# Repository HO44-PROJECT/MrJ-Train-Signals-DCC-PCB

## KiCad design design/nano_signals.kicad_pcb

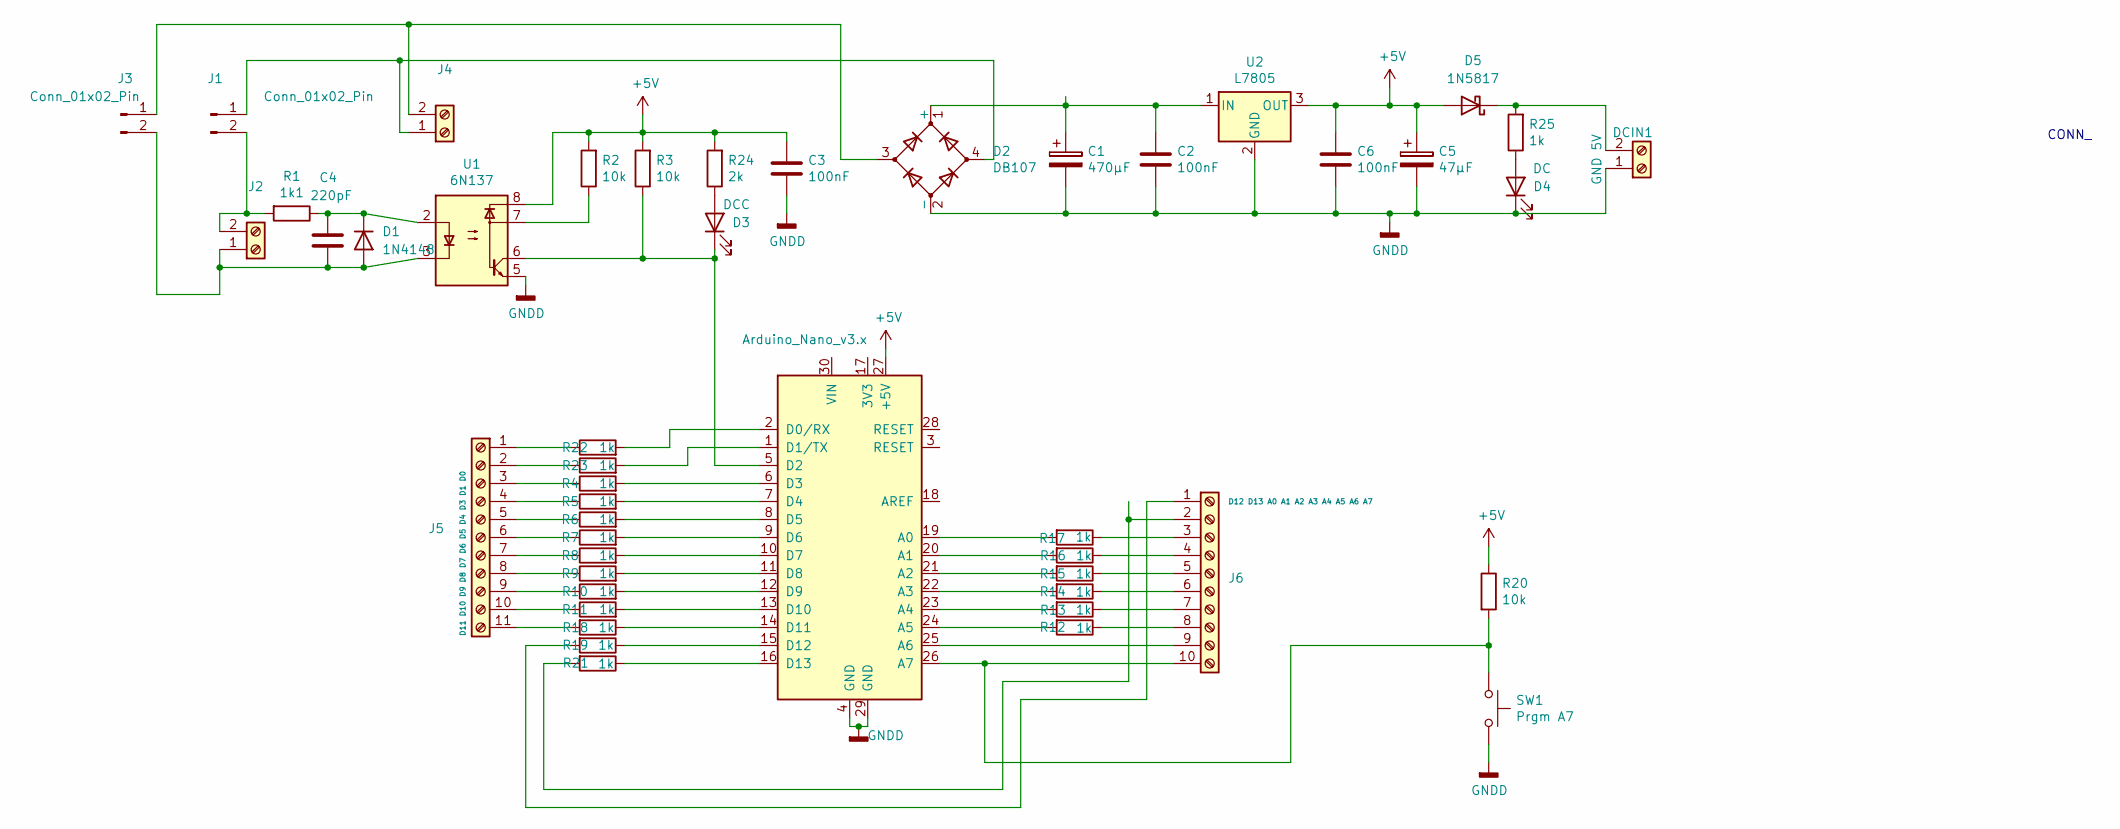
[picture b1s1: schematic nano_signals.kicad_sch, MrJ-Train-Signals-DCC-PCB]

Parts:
A1: Arduino_Nano_v3.x; Arduino_Nano
C1: 470µF; CP_Radial_D8.0mm_P3.50mm
C2, C6: 100nF; C_Disc_D4.7mm_W2.5mm_P5.00mm
C3: 100nF; C_Disc_D4.3mm_W1.9mm_P5.00mm
C4: 220pF; C_Disc_D4.7mm_W2.5mm_P5.00mm
C5: 47µF; CP_Radial_D5.0mm_P2.00mm
D1: 1N4148; D_DO-35_SOD27_P7.62mm_Horizontal
D2: DB107; Diode_Bridge_DIP-4_W7.62mm_P5.08mm
D3: DCC; LED_D3.0mm
D4: DC; LED_D3.0mm
D5: 1N5817; D_DO-41_SOD81_P10.16mm_Horizontal
DCIN1: GND 5V; TerminalBlock_4Ucon_1x02_P3.50mm_Horizontal
J1, J3: Conn_01x02_Pin; PinHeader_1x02_P2.54mm_Vertical
J2, J4: DCC; TerminalBlock_4Ucon_1x02_P3.50mm_Horizontal
J5: D11 D10 D9 D8 D7 D6 D5 D4 D3 D1 D0; TerminalBlock_4Ucon_1x11_P3.50mm_Horizontal
J6: D12 D13 A0 A1 A2 A3 A4 A5 A6 A7; TerminalBlock_4Ucon_1x10_P3.50mm_Horizontal
R1: 1k1; R_Axial_DIN0207_L6.3mm_D2.5mm_P10.16mm_Horizontal
R2, R3, R20: 10k; R_Axial_DIN0204_L3.6mm_D1.6mm_P7.62mm_Horizontal
R4, R5, R6, R7, R8, R9, R10, R11, R12, R13, R14, R15, R16, R17, R18, R19, R21, R22, R23: 1k; R_1206_3216Metric_Pad1.30x1.75mm_HandSolder
R24: 2k; R_Axial_DIN0204_L3.6mm_D1.6mm_P7.62mm_Horizontal
R25: 1k; R_Axial_DIN0204_L3.6mm_D1.6mm_P7.62mm_Horizontal
SW1: Prgm A7; SW_PUSH_6mm_H5mm
U1: 6N137; DIP-8_W7.62mm
U2: L7805; TO-220-3_Horizontal_TabDown

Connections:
+5V: A1.27 (+5V), C3.1, C5.1, C6.1, D5.2 (A), R2.2, R3.2, R20.1, R24.2, U1.8, U2.3 (OUT)
GNDD: A1.4 (GND), A1.29 (GND), C1.2, C2.2, C3.2, C5.2, C6.2, D2.2 (-), D4.1 (K), DCIN1.1, SW1.2, U1.5, U2.2 (GND)
unnamed: A1.19 (A0), R17.2
unnamed: A1.20 (A1), R16.2
unnamed: A1.21 (A2), R15.2
unnamed: A1.22 (A3), R14.2
unnamed: A1.23 (A4), R13.2
unnamed: A1.24 (A5), R12.2
unnamed: A1.25 (A6), J6.9
unnamed: A1.26 (A7), J6.10, R20.2, SW1.1
unnamed: A1.2 (D0/RX), R22.2
unnamed: A1.1 (D1/TX), R23.2
unnamed: A1.5 (D2), D3.1 (K), R3.1, U1.6
unnamed: A1.6 (D3), R4.2
unnamed: A1.7 (D4), R5.2
unnamed: A1.8 (D5), R6.2
unnamed: A1.9 (D6), R7.2
unnamed: A1.10 (D7), R8.2
unnamed: A1.11 (D8), R9.2
unnamed: A1.12 (D9), R10.2
unnamed: A1.13 (D10), R11.2
unnamed: A1.14 (D11), R18.1
unnamed: A1.15 (D12), R19.1
unnamed: A1.16 (D13), R21.1
unnamed: C4.2, D1.2 (A), J2.1, J3.2, U1.3
unnamed: C4.1, D1.1 (K), R1.1, U1.2
unnamed: C1.1, C2.1, D2.1 (+), U2.1 (IN)
unnamed: D3.2 (A), R24.1
unnamed: D4.2 (A), R25.1
unnamed: D5.1 (K), DCIN1.2, R25.2
unnamed: D2.4, J1.1, J4.1
unnamed: J1.2, J2.2, R1.2
unnamed: D2.3, J3.1, J4.2
unnamed: J5.1, R22.1
unnamed: J5.2, R23.1
unnamed: J5.3, R4.1
unnamed: J5.4, R5.1
unnamed: J5.5, R6.1
unnamed: J5.6, R7.1
unnamed: J5.7, R8.1
unnamed: J5.8, R9.1
unnamed: J5.9, R10.1
unnamed: J5.10, R11.1
unnamed: J5.11, R18.2
unnamed: J6.1, R19.2
unnamed: J6.2, R21.2
unnamed: J6.3, R17.1
unnamed: J6.4, R16.1
unnamed: J6.5, R15.1
unnamed: J6.6, R14.1
unnamed: J6.7, R13.1
unnamed: J6.8, R12.1
unnamed: R2.1, U1.7

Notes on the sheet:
CONN_

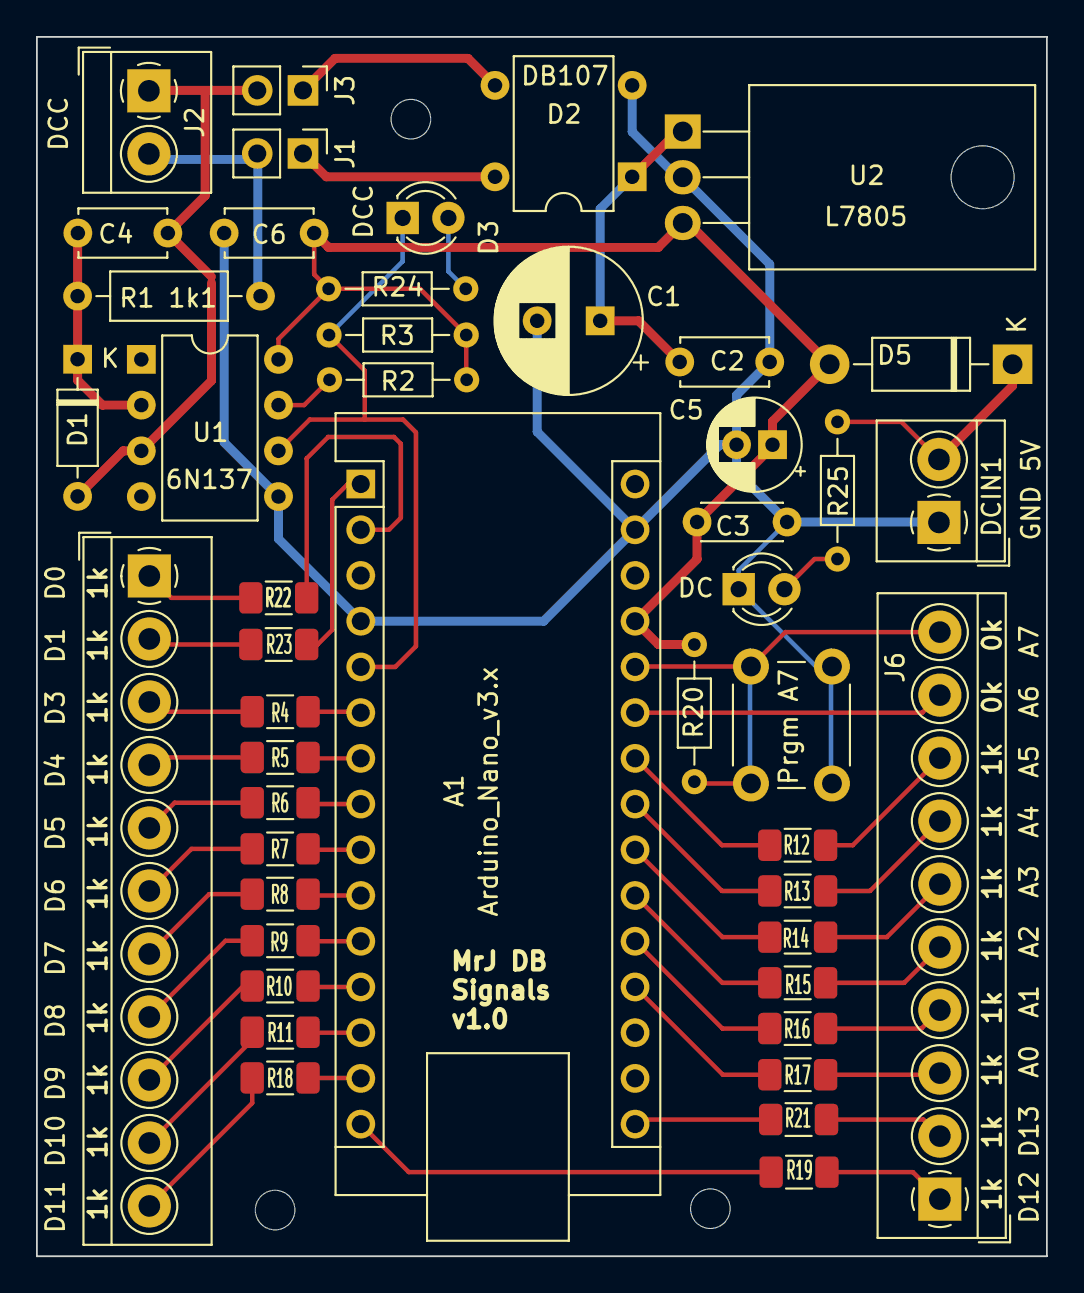
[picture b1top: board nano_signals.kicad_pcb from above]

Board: 2 copper layers, 56.1 x 67.7 mm, 46 parts (0 on the bottom side), 53 nets.

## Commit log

2024-11-16 v2 & production
2024-11-16 no message
2024-11-16 Final V1 & Production
2024-11-16 v1 & production
2024-11-16 3d views
